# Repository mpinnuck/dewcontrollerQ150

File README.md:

# Q150 Dew Controller

An intelligent dew prevention system for astronomical telescopes and optical equipment, featuring automatic humidity monitoring and adaptive heating control.

## Overview

The Q150 Dew Controller uses precise temperature and humidity sensing to calculate dew point and automatically control heater power to prevent condensation on telescope optics. The system features both WiFi web interface and Bluetooth Low Energy (BLE) connectivity for remote monitoring and configuration.

## Key Features

### Environmental Monitoring
- **SHT45 Sensor**: High-precision temperature (±0.1°C) and humidity (±1.5% RH) measurement
- **Real-time Dew Point Calculation**: Continuous monitoring of dew point temperature
- **Spread Tracking**: Calculates temperature margin above dew point

### Intelligent Heating Control
- **Adaptive Power Control**: Automatically adjusts heater power based on dew point spread
- **Configurable Power Table**: Up to 5 spread→power mapping points for custom response curves
- **Manual Override**: Direct power control via slider (0-100%)
- **PWM Output**: Smooth, efficient heater control on D8 pin

### Connectivity

#### WiFi Web Interface
- **Responsive Design**: Works on desktop, tablet, and mobile devices
- **Real-time Updates**: Live sensor readings every 2 seconds
- **Configuration**: WiFi credentials, timezone, and heater settings
- **Fast Disconnect Detection**: 1-second timeout for quick offline status
- **Automatic Reconnection**: Seamless recovery when connection is restored

#### Bluetooth Low Energy (BLE)
- **Desktop Management App**: Python-based configuration tool
- **Auto-connect**: Automatically finds and connects to Q150 devices
- **Config Management**: Read/write heater settings and spread table
- **Cross-platform**: macOS, Windows, Linux support

### Time & Logging
- **NTP Time Sync**: Automatic time synchronization via internet
- **Timezone Support**: 18 worldwide timezones with automatic DST adjustment
- **POSIX Timezones**: Full support for complex timezone rules
- **Timestamped Logs**: Real date/time stamps when NTP synced, boot time otherwise

### Network Modes
- **Station Mode**: Connects to existing WiFi network
- **Fallback AP Mode**: Creates "Q150Dew" access point if connection fails
- **mDNS**: Access via `q150dew.local` hostname
- **Persistent Settings**: WiFi credentials stored in flash

## Hardware

### Microcontroller
- **Board**: Seeed Studio XIAO ESP32-S3
- **CPU**: Dual-core Xtensa 32-bit LX7 @ 240MHz
- **Memory**: 512KB SRAM, 8MB Flash
- **Connectivity**: WiFi 802.11 b/g/n, BLE 5.0

### Sensor
- **Model**: Sensirion SHT45
- **Interface**: I2C (SDA=D4, SCL=D5)
- **Accuracy**: ±0.1°C, ±1.5% RH
- **Range**: -40°C to 125°C, 0-100% RH

### Output
- **PWM Pin**: D8 (Pin 9)
- **Frequency**: 1 kHz
- **Resolution**: 8-bit (0-255)
- **Driver**: External MOSFET (FQP30N06) for high-current loads

### PCB
- Custom KiCAD design in `hardware/dewcontrollerQ150/`
- Gerber files ready for fabrication in `hardware/dewcontrollerQ150/pcbfiles/`

### Enclosure
- FreeCAD design in `housing/Q150DewController.FCStd`
- STL files for 3D printing in `housing/stl/`

## Firmware

**Version**: 2.1  
**File**: `firmware/dewcontrollerq150/dewcontrollerq150.ino`

### Dependencies
Install via Arduino Library Manager:
- ArduinoJson (6.x)
- Adafruit SHT4x Library
- ESP32 BLE Arduino

### Compilation
1. Install [Arduino IDE](https://www.arduino.cc/en/software) or [PlatformIO](https://platformio.org/)
2. Install ESP32 board support: https://docs.espressif.com/projects/arduino-esp32/
3. Select board: **XIAO_ESP32S3**
4. Open `firmware/dewcontrollerq150/dewcontrollerq150.ino`
5. Set `DEBUG` to `0` for release build (line 16)
6. Compile and upload

### Configuration
Default WiFi fallback credentials:
- **SSID**: `Q150Dew`
- **Password**: `tinka`

Default timezone: Australia (Sydney/Melbourne) with automatic DST

## Desktop Application

**File**: `app/q150dewcontroller.py`

### Features
- Auto-discovery and connection to Q150 devices
- Read device info and current configuration
- Edit and update:
  - Heater enable/disable
  - Spread→Power table (5 entries)
  - WiFi SSID and password
  - Timezone selection
- Real-time status monitoring
- Cross-platform (macOS, Windows, Linux)

### Requirements
```bash
pip install bleak
```

### Running
```bash
cd app
python q150dewcontroller.py
```

### Building Executable
```bash
cd app
pyinstaller q150dewcontroller.spec --noconfirm
```

Built app will be in `app/dist/q150dewcontroller.app` (macOS) or `app/dist/q150dewcontroller.exe` (Windows)

## Usage

### Initial Setup
1. Power on the Q150 Dew Controller
2. Connect to WiFi AP "Q150Dew" (password: "tinka")
3. Open browser to `http://192.168.4.1` or `http://q150dew.local`
4. Configure your WiFi credentials and timezone
5. Device will restart and connect to your network

### Web Interface
Access via `http://q150dew.local` or device IP address

**Main Panel**:
- Temperature, humidity, dew point, and spread readings
- Heater status (ON/OFF) and current power level
- WiFi connection status and signal strength
- Current time (when NTP synced)

**Control Panel**:
- **Toggle Heater**: Enable/disable automatic control
- **Manual Power Slider**: Override automatic control (0-100%)
- **Spread Table**: Configure up to 5 spread→power points
- **WiFi Config**: Update credentials and timezone

**System Log**:
- Real-time event log with timestamps
- Pause/resume log updates
- Connection status, sensor readings, configuration changes

### BLE Management App
1. Launch `q150dewcontroller` application
2. Click **Scan & Connect** to find devices
3. Device info and status display automatically
4. Edit configuration settings as needed
5. Click **Write Config** to save changes to device

### Power Table Configuration
Define the relationship between temperature spread (T - Tdew) and heater power:

Example table:
| Spread (°C) | Power (%) |
|-------------|-----------|
| 0.0         | 100       |
| 2.0         | 75        |
| 5.0         | 50        |
| 10.0        | 25        |
| 15.0        | 0         |

The controller interpolates between points for smooth power transitions.

## Technical Details

### API Endpoints

**GET /api/status**
Returns current sensor readings, heater status, WiFi info, and time

**POST /api/toggle**
Toggles heater enabled state

**POST /api/power**
Sets manual power override (0-100)

**POST /api/config**
Updates heater configuration and spread table

**POST /api/wifi**
Updates WiFi credentials and timezone (triggers restart)

**GET /api/log**
Returns system event log

### BLE Characteristics

**Service UUID**: `12345678-1234-1234-1234-123456789abc`

- **INFO**: Device information (read-only)
- **STATUS**: Real-time sensor data (read/notify)
- **CONFIG**: Configuration settings (read/write)
- **CMD**: Command interface (write)

### Dew Point Calculation
Uses Magnus formula:
```
γ(T,RH) = ln(RH/100) + (b×T)/(c+T)
Tdew = (c×γ)/(b-γ)
```
Where: b = 17.62, c = 243.12°C

### Timezone Support
18 timezones with POSIX format including:
- UTC, UK (GMT/BST)
- Europe (CET, EET)
- US (EST, CST, MST, PST, AKST, HST)
- Australia (AEST, ACST, AWST)
- New Zealand, Japan, China, India, Middle East

Automatic daylight saving time adjustments.

## Development

### Repository Structure
```
dewcontrollerQ150/
├── firmware/
│   └── dewcontrollerq150/
│       └── dewcontrollerq150.ino    # ESP32 firmware
├── app/
│   ├── q150dewcontroller.py         # Python BLE app
│   └── q150dewcontroller.spec       # PyInstaller spec
├── hardware/
│   └── dewcontrollerQ150/
│       ├── dewcontrollerQ150.kicad_pcb   # PCB design
│       ├── dewcontrollerQ150.kicad_sch   # Schematic
│       └── pcbfiles/                     # Gerber files
└── housing/
    ├── Q150DewController.FCStd      # FreeCAD model
    └── stl/                         # 3D print files
```

### Version History
- **v2.1**: Debounced slider, improved disconnect detection, timezone config in BLE app
- **v2.0**: WiFi configuration, NTP time sync, responsive mobile UI
- **v1.3**: Enhanced BLE, power table configuration
- **v1.2**: PCB revision, housing design
- **v1.0**: Initial production version

## Troubleshooting

**Device won't connect to WiFi**
- Check SSID and password in WiFi Config
- Ensure 2.4GHz WiFi (5GHz not supported)
- Device will fall back to AP mode "Q150Dew" if connection fails

**Web interface shows "Disconnected"**
- Check device is powered on
- Verify you're on the same network
- Try accessing by IP address instead of hostname

**NTP time not syncing**
- Requires internet connection
- Check timezone setting is correct
- Time will show "Not synced" until successful NTP update

**Heater not responding**
- Check heater is enabled (not just power set)
- Verify MOSFET and heater connections
- Check spread table has valid entries

## License

Copyright © 2026 Mark Pinnuck

## Acknowledgments

- Sensirion for SHT45 sensor library
- Seeed Studio for XIAO ESP32-S3 platform
- Arduino and ESP32 communities

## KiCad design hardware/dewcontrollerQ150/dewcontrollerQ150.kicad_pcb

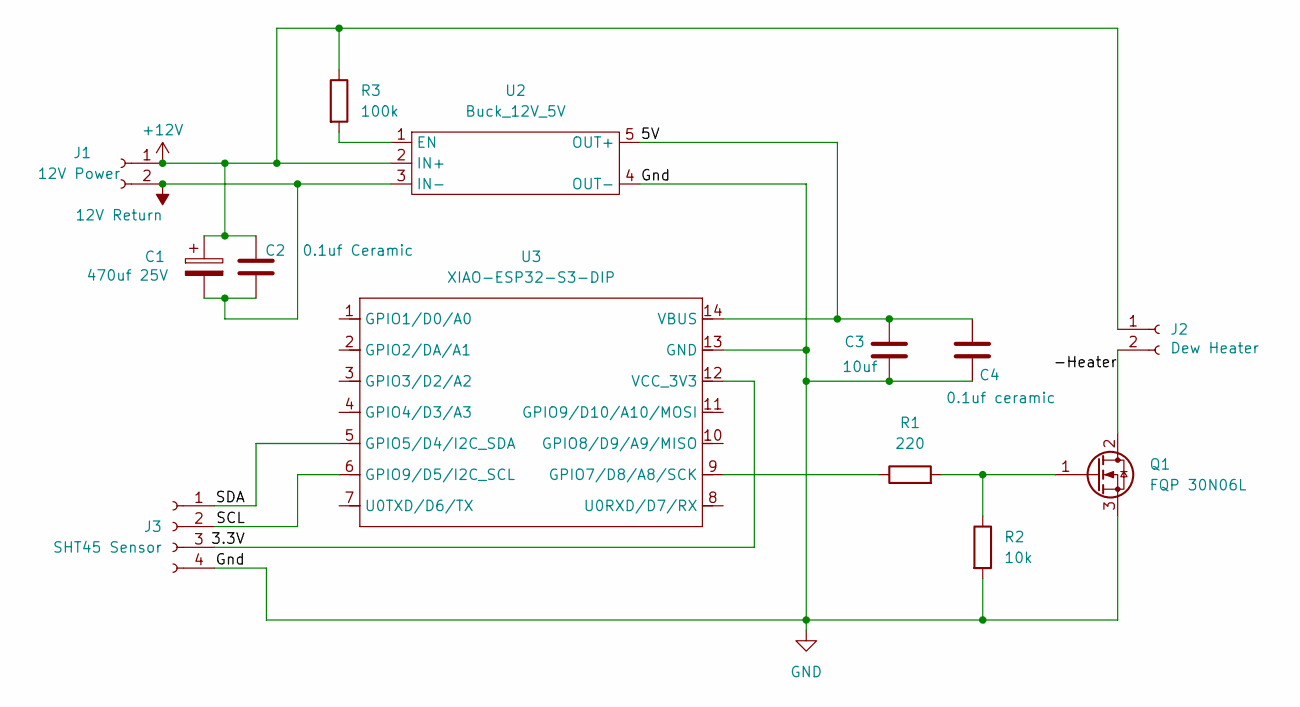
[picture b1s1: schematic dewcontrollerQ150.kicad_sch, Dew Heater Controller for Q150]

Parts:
C1: 470uf 25V; CP_Radial_D10.0mm_P5.00mm
C2: 0.1uf Ceramic; C_Disc_D5.1mm_W3.2mm_P5.00mm
C3: 10uf; C_Disc_D5.1mm_W3.2mm_P5.00mm
C4: 0.1uf ceramic; C_Disc_D5.1mm_W3.2mm_P5.00mm
J1: 12V Power; JST_XH_B2B-XH-A_1x02_P2.50mm_Vertical
J2: Dew Heater; JST_XH_B2B-XH-A_1x02_P2.50mm_Vertical
J3: SHT45 Sensor; JST_XH_B4B-XH-A_1x04_P2.50mm_Vertical
Q1: FQP 30N06L; TO-220-3_Vertical
R1: 220; R_Axial_DIN0207_L6.3mm_D2.5mm_P7.62mm_Horizontal
R2: 10k; R_Axial_DIN0207_L6.3mm_D2.5mm_P7.62mm_Horizontal
R3: 100k; R_Axial_DIN0207_L6.3mm_D2.5mm_P7.62mm_Horizontal
U2: Buck_12V_5V; MP_Buck_Tunghey_5Pin_THT
U3: XIAO-ESP32-S3-DIP; XIAO-ESP32S3-DIP

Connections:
12V Return: C1.2, C2.2, J1.2, U2.3 (IN-)
+12V: C1.1, C2.1, J1.1, J2.1, R3.1, U2.2 (IN+)
/3.3V: J3.3, U3.12 (VCC_3V3)
/5V: C3.1, C4.1, U2.5 (OUT+), U3.14 (VBUS)
/-Heater: J2.2, Q1.2 (D)
/SCL: J3.2, U3.6 (GPIO9/D5/I2C_SCL)
/SDA: J3.1, U3.5 (GPIO5/D4/I2C_SDA)
GND: C3.2, C4.2, J3.4, Q1.3 (S), R2.2, U2.4 (OUT-), U3.13 (GND)
unnamed: Q1.1 (G), R1.2, R2.1
unnamed: R3.2, U2.1 (EN)
unnamed: R1.1, U3.9 (GPIO7/D8/A8/SCK)

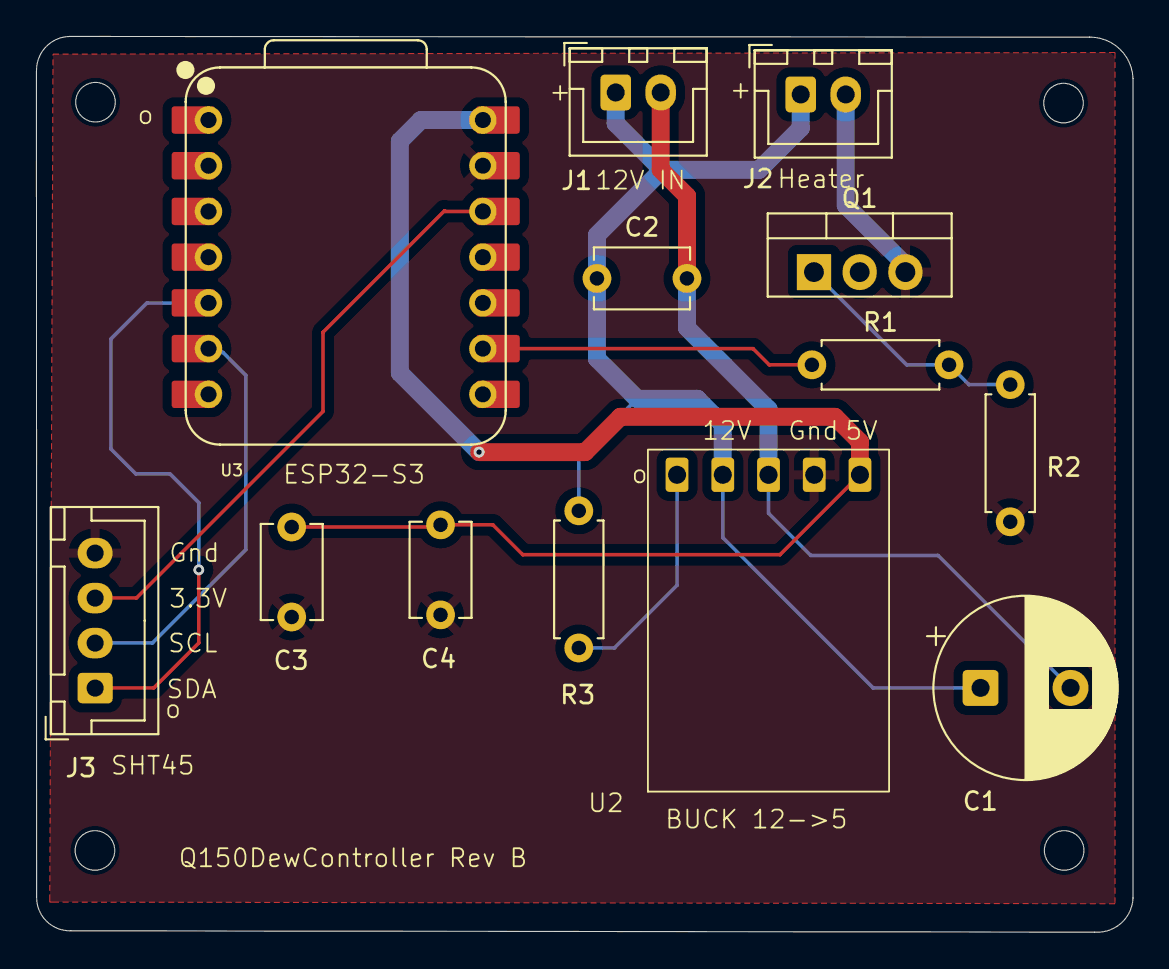
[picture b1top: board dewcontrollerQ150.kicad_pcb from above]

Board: 2 copper layers, 60.9 x 49.8 mm, 17 parts (0 on the bottom side), 11 nets.

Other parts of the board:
mh1, mh2, mh3, mh4: MountingHole_2.2mm_M2

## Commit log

2026-01-28 v0.1 initial
2026-01-29 V0.5 switched to ESP32S3
2026-01-29 V0.51 updated KiCAD schematic with S3
2026-01-30 v0.52 inprogress about to restructure BLE workflow
2026-01-31 v0.6 tidy up code
2026-02-02 v0.7 Latest CAD and KiCAD files
2026-02-05 v1.0 First production version
2026-02-06 v1.1 tidy up GUI and version number
2026-02-07 V1.2 PCB fixed ESP32S3 and FQP30N06 footprints
2026-02-07 v1.2b Changed esp32-S3 to correct footprint
2026-02-14 v1.2b housing updates
2026-02-14 V1.2c updated power table in ino
2026-02-14 v1.2d added windows s.spec file for python app
2026-02-16 v2.0 added wifi,NTP Web GUI
2026-02-16 v2.0 adde wifi, ntp Web UI
2026-02-17 V2.1 tidy up disconnect reconnect
2026-02-17 V2.1a added README
2026-02-17 v2.1b tidy up git files
2026-02-17 v2.1c added nextxday.pdf to gitignore
2026-02-17 v2.1d added windows build comments at top of code
2026-03-16 v3.0 correct spread-to-power lookup logic and load saved config into web UI on page load
2026-04-05 V4.0 review and bug fixes
2026-04-05 v4.1 bug fix
2026-04-05 V4.2 updated heater logic
